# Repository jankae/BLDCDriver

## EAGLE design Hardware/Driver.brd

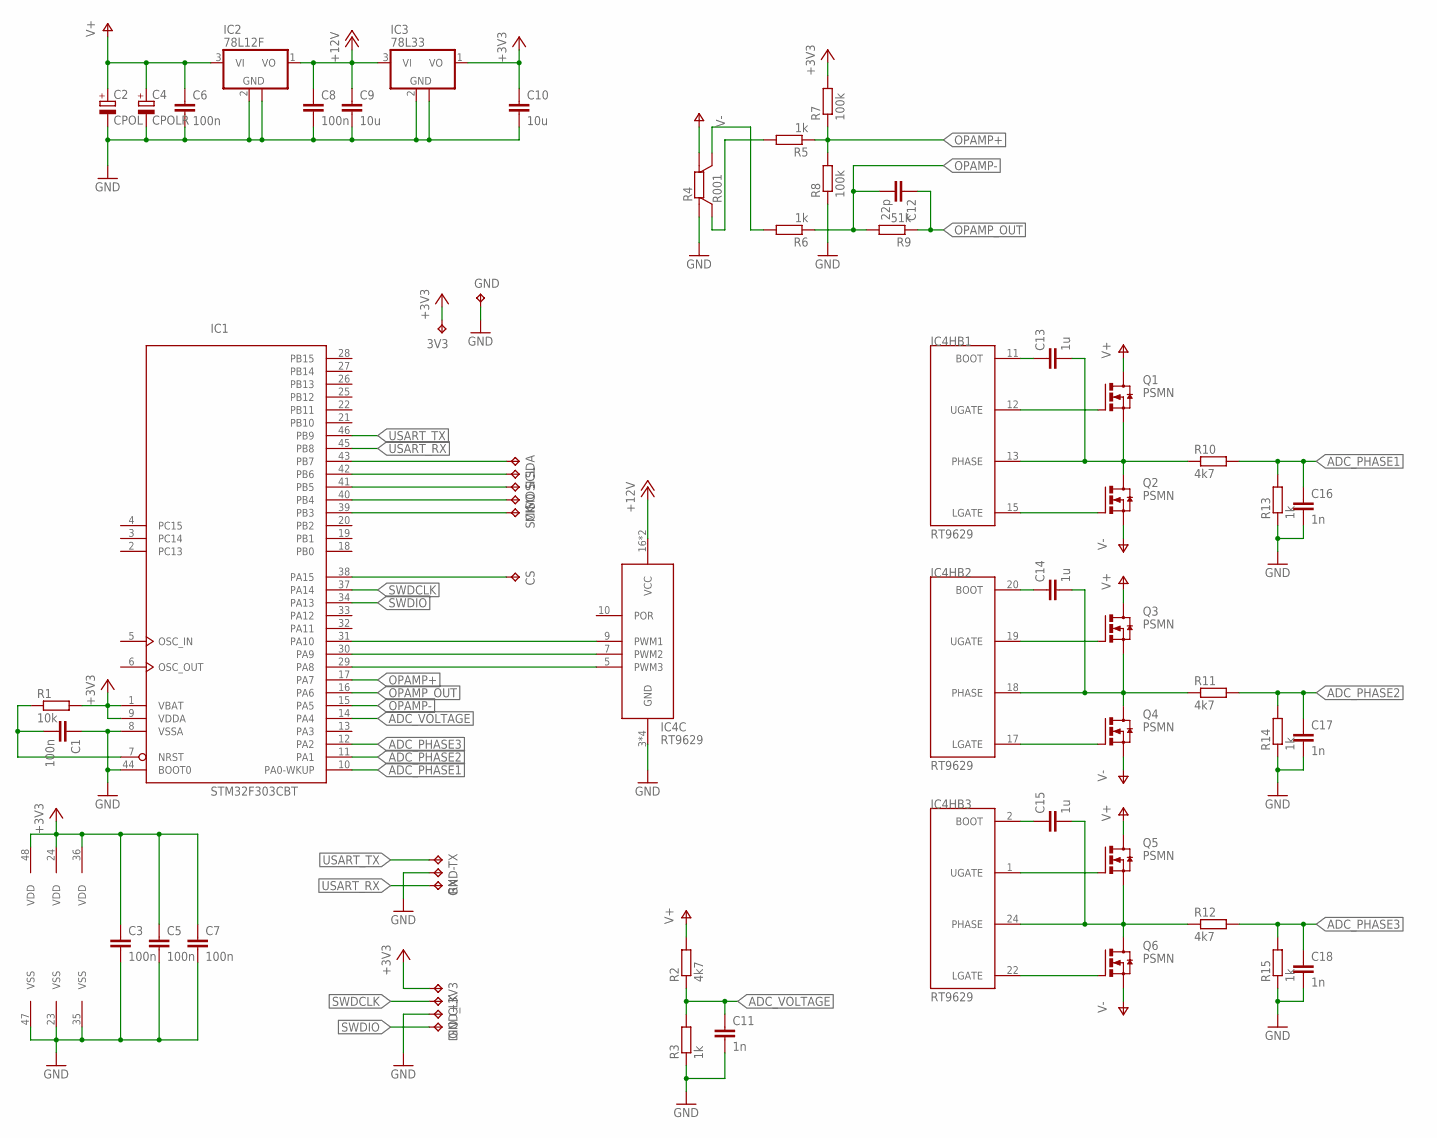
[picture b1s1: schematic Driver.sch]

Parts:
3V3: TPTP10SQ; TP10SQ
+3V3: TPTP15R; TP15R
C1, C3, C5, C6, C7, C8: 100n; C0603K
C2: CPOL; SIDEWAYS-5.08
C4: CPOLR; SIDEWAYS-5.08R
C9, C10: 10u; C1206K
C11, C16, C17, C18: 1n; C0603K
C12: 22p; C0603K
C13, C14, C15: 1u; C0603K
CLK: TPTP15R; TP15R
CS: TPTP10SQ; TP10SQ
DIO: TPTP15R; TP15R
GND: TPTP10SQ; TP10SQ
GND-: TPTP15SQ; TP15SQ
GND_: TPTP15SQ; TP15SQ
IC1: STM32F303CBT; LQFP48
IC2: 78L12F; SOT89
IC3: 78L33; SOT89
IC4: RT9629; WQFN24
MISO: TPTP10SQ; TP10SQ
MOSI: TPTP10SQ; TP10SQ
Q1, Q2, Q3, Q4, Q5, Q6: PSMN; SOT669
R1: 10k; R0603
R2, R10, R11, R12: 4k7; R0603
R3, R5, R6, R13, R14, R15: 1k; R0603
R4: R001; WSK1216
R7, R8: 100k; R0603
R9: 51k; R0603
RX: TPTP15R; TP15R
SCK: TPTP10SQ; TP10SQ
SCL: TPTP10SQ; TP10SQ
SDA: TPTP10SQ; TP10SQ
TX: TPTP15R; TP15R

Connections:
+3V3: 3V3.TP, +3V3.TP, C3.1, C5.1, C7.1, C10.1, IC1.1 (VBAT), IC1.9 (VDDA), IC1.24 (VDD), IC1.36 (VDD), IC1.48 (VDD), IC3.1 (VO), R1.2, R7.2
+12V: C8.1, C9.1, IC2.1 (VO), IC3.3 (VI), IC4.16 (VCC), IC4.21 (VCC)
ADC_PHASE1: C16.1, IC1.10 (PA0-WKUP), R10.2, R13.2
ADC_PHASE2: C17.1, IC1.11 (PA1), R11.2, R14.2
ADC_PHASE3: C18.1, IC1.12 (PA2), R12.2, R15.2
ADC_VOLTAGE: C11.1, IC1.14 (PA4), R2.1, R3.2
GND: C1.1, C2.-, C3.2, C4.-, C5.2, C6.2, C7.2, C8.2, C9.2, C10.2, C11.2, C16.2, C17.2, C18.2, GND.TP, GND-.TP, GND_.TP, IC1.8 (VSSA), IC1.23 (VSS), IC1.35 (VSS), IC1.44 (BOOT0), IC1.47 (VSS), IC2.2 (GND), IC2.2@1 (GND), IC3.2 (GND), IC3.2@1 (GND), IC4.3 (GND), IC4.14 (GND), IC4.23 (GND), IC4.E (GND), R3.1, R4.B, R8.1, R13.1, R14.1, R15.1
I2C_SCL: IC1.42 (PB6), SCL.TP
I2C_SDA: IC1.43 (PB7), SDA.TP
unnamed: IC4.12 (UGATE), Q1.4 (G)
unnamed: IC4.15 (LGATE), Q2.4 (G)
unnamed: C13.1, IC4.11 (BOOT)
unnamed: C14.1, IC4.20 (BOOT)
unnamed: IC4.19 (UGATE), Q3.4 (G)
unnamed: IC4.17 (LGATE), Q4.4 (G)
unnamed: C15.1, IC4.2 (BOOT)
unnamed: IC4.1 (UGATE), Q5.4 (G)
unnamed: IC4.22 (LGATE), Q6.4 (G)
unnamed: C1.2, IC1.7 (NRST), R1.1
unnamed: R4.SA, R6.2
unnamed: R4.SB, R5.2
OPAMP+: IC1.17 (PA7), R5.1, R7.1, R8.2
OPAMP-: C12.2, IC1.15 (PA5), R6.1, R9.2
OPAMP_OUT: C12.1, IC1.16 (PA6), R9.1
PHASE1: C13.2, IC4.13 (PHASE), Q1.1 (S), Q1.2 (S), Q1.3 (S), Q2.MB (D), R10.1
PHASE2: C14.2, IC4.18 (PHASE), Q3.1 (S), Q3.2 (S), Q3.3 (S), Q4.MB (D), R11.1
PHASE3: C15.2, IC4.24 (PHASE), Q5.1 (S), Q5.2 (S), Q5.3 (S), Q6.MB (D), R12.1
PWM1: IC1.31 (PA10), IC4.9 (PWM1)
PWM2: IC1.30 (PA9), IC4.7 (PWM2)
PWM3: IC1.29 (PA8), IC4.5 (PWM3)
SPI_MISO: IC1.40 (PB4), MISO.TP
SPI_MOSI: IC1.41 (PB5), MOSI.TP
SPI_NSS: CS.TP, IC1.38 (PA15)
SPI_SCK: IC1.39 (PB3), SCK.TP
SWDCLK: CLK.TP, IC1.37 (PA14)
SWDIO: DIO.TP, IC1.34 (PA13)
USART_RX: IC1.45 (PB8), RX.TP
USART_TX: IC1.46 (PB9), TX.TP
V+: C2.+, C4.+, C6.1, IC2.3 (VI), Q1.MB (D), Q3.MB (D), Q5.MB (D), R2.2
V-: Q2.1 (S), Q2.2 (S), Q2.3 (S), Q4.1 (S), Q4.2 (S), Q4.3 (S), Q6.1 (S), Q6.2 (S), Q6.3 (S), R4.A

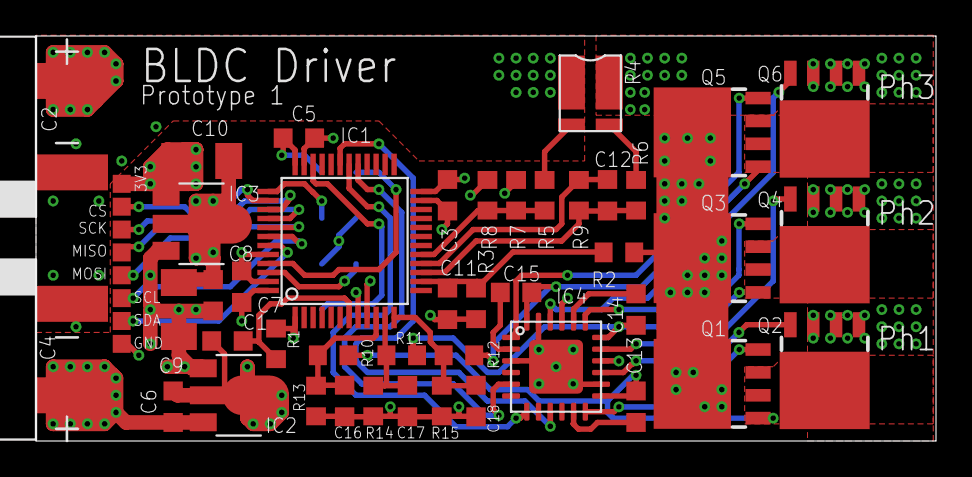
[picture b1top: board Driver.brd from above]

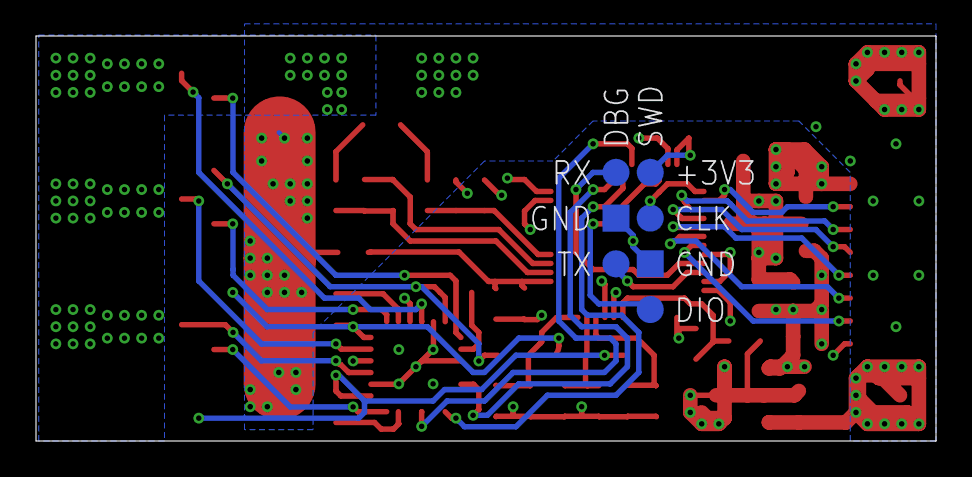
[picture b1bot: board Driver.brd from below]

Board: 4 copper layers, 50.0 x 22.5 mm, 58 parts (7 on the bottom side), 40 nets.

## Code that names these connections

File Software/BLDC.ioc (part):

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Mcu.Name=STM32F303C(6-8)Tx
Mcu.Package=LQFP48
Mcu.UserName=STM32F303C6Tx
PA0.Mode=IN1-Single-Ended
PA0.Signal=ADC1_IN1
PA1.Mode=IN2-Single-Ended
PA1.Signal=ADC1_IN2
PA10.Signal=S_TIM1_CH3
PA13.Mode=Serial_Wire
PA13.Signal=SYS_JTMS-SWDIO
PA14.Mode=Serial_Wire
PA14.Signal=SYS_JTCK-SWCLK
PA15.Mode=NSS_Signal_Hard_Input
PA15.Signal=SPI1_NSS
PA2.Mode=IN3-Single-Ended
PA2.Signal=ADC1_IN3
PA4.Mode=IN1-Single-Ended
PA4.Signal=ADC2_IN1
PA5.Mode=Standalone
PA5.Signal=OPAMP2_VINM
PA6.Mode=Standalone
PA6.Signal=OPAMP2_VOUT
PA7.Mode=Standalone
PA7.Signal=OPAMP2_VINP
PA8.Signal=S_TIM1_CH1
PA9.Signal=S_TIM1_CH2
PB11.Mode=Asynchronous
PB11.Signal=USART3_RX
PB3.Mode=Full_Duplex_Slave
PB3.Signal=SPI1_SCK
PB4.Mode=Full_Duplex_Slave
PB4.Signal=SPI1_MISO
PB5.Mode=Full_Duplex_Slave
PB5.Signal=SPI1_MOSI
PB6.Mode=I2C
PB6.Signal=I2C1_SCL
PB7.Mode=I2C
PB7.Signal=I2C1_SDA
PB8.GPIOParameters=GPIO_Speed,GPIO_Label
PB8.GPIO_Label=TRIGGER_PIN
PB8.GPIO_Speed=GPIO_SPEED_FREQ_HIGH
PB8.Signal=GPIO_Output
PB9.Mode=Asynchronous
PB9.Signal=USART3_TX
RCC.HSEPLLFreq_Value=8000000
RCC.HSE_VALUE=8000000
RCC.SYSCLKFreq_VALUE=64000000
RCC.SYSCLKSourceVirtual=RCC_SYSCLKSOURCE_PLLCLK

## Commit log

2018-08-16 Hardware prototype 1 + CubeMX files
2018-08-16 Fix makefile and add eclipse ignores
2018-08-16 lowest level phase driver + CubeMX update
2018-08-17 commutation detection + better separation of lowlevel/highlevel driver
2018-08-22 Basic BLDC driver, stubs for supporting HAL functions
2018-08-22 rename namespace Core -> HAL
2018-08-25 Dimensioning R + C
2018-08-25 Switched CubeMX to correct MCU version + basic logging module
2018-08-25 Bugfixes: ADC buffer length and PWM start
2018-08-27 Detektor experiments, driver improved, motor starts sometimes and runs smooth
2018-08-28 PI/6 inductance sensing, some improvements to the still primitive start routine
2018-09-23 Improved RAM usage, found some problems with interrupt priorities
2018-09-24 Implemented driver as state machine (mostly backfires at the moment)
2018-09-28 Sensing BEMF during PWM off, motor starts reliable
2018-10-01 Track DC bus voltage and switch to idling when voltage too high (avoids problems with regenerative braking with sink-capable supply)
2018-10-01 removed no longer needed code
2018-10-01 preparations for persistent motor data and current/voltages measurements
2018-10-02 Partial Core::Propeller implementation + basic UART communication
2018-10-02 Fixed bugs in communication and propeller calculations + some motor characterisation methods
2018-10-03 First wind estimation test
2018-10-03 Commutation improvements, electrical RPM up to 50000
2018-10-04 Energy measurement and experimental inertia sensing
2018-12-13 T440 changes
2019-01-08 Detect a backfiring motor and start again
2019-01-13 CubeMX regenerate + I2C slave driver code
2019-01-14 Baudrate 500000, I2C slave fixed
2019-02-12 Percentage control via I2C implemented
2019-02-14 Coherent mapping from inductance sensing to driver steps
2019-02-16 Logging using DMA (issues with CubeMX regenerating), motor startup almost reliable
2019-02-18 Measure and report motor data
2019-07-10 Cleanup of test code
2019-07-10 gitignore update
2019-12-08 PDF of schematic
2020-01-07 Eclipse update
2020-01-07 CubeMX update
2020-01-07 Integral limit reduced (more stable at high speed and low load
